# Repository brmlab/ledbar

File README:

eagle: PCB design
arduino: Semi-generic TLC59116 library and ledbar Arduino firmware
host: C frontend
host_python: Python frontend

Both the C frontend and the Python frontend have their pros and cons.
We still use both and it's unclear which one will prevail. Try them
and use the one you like better.

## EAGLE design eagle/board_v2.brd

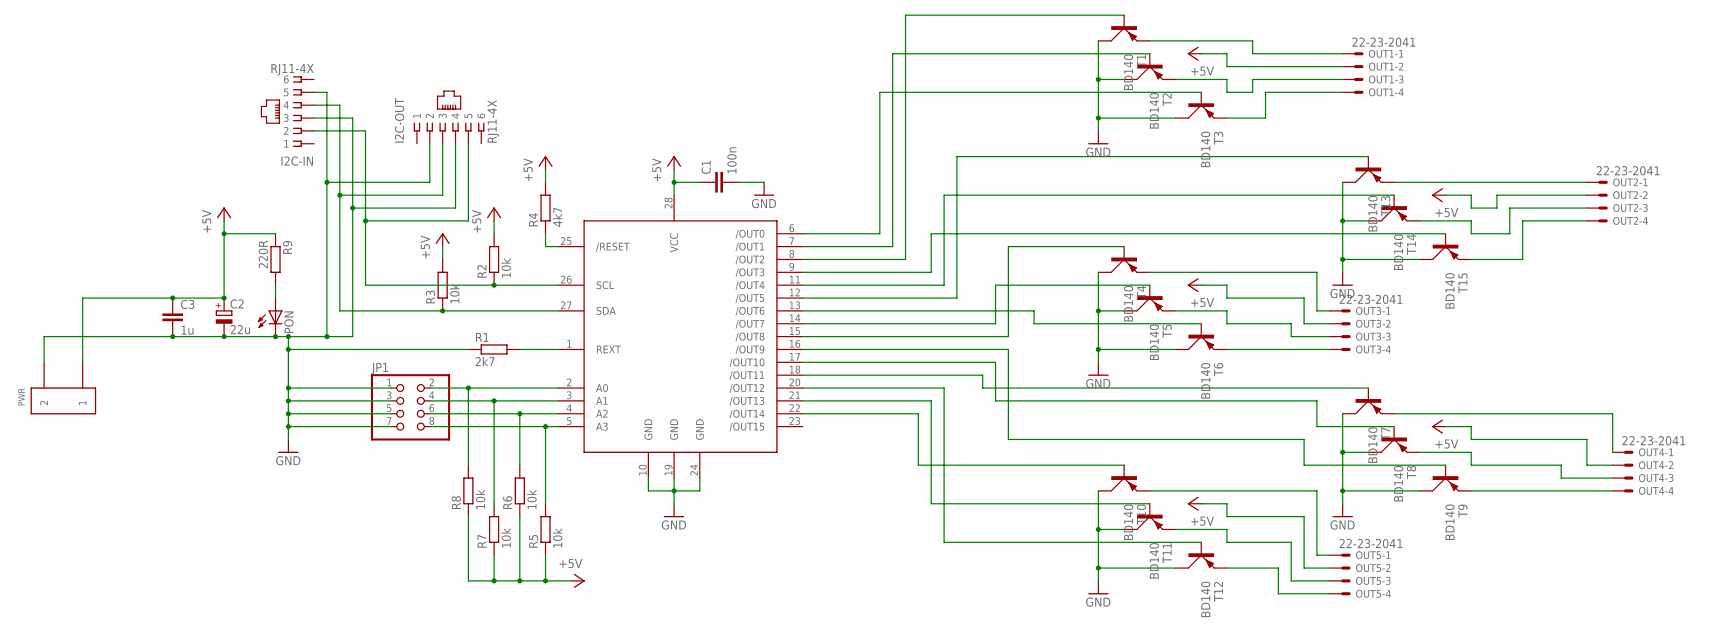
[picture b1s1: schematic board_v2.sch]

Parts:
C1: 100n; C1206
C2: 22u; E2,5-5
C3: 1u; C1206
I2C-IN: RJ11-4X; RJ11-NO_SHIELD
I2C-OUT: RJ11-4X; RJ11-NO_SHIELD; MPN 6609214-3
IC1: TLC59116; TSSOP28
JP1: PINHD-2X4; 2X04
OUT1, OUT2, OUT3, OUT4, OUT5: 22-23-2041
PON: LEDCHIPLED_1206; CHIPLED_1206
PWR: ARK210/2EX
R1: 2k7; R1206
R2, R3, R5, R6, R7, R8: 10k; R1206
R4: 4k7; R1206
R9: 220R; R1206
T1, T2, T3, T4, T5, T6, T7, T8, T9, T10, T11, T12, T13, T14, T15: BD140; TO126AV

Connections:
+5V: C1.1, C2.+, C3.1, IC1.28 (VCC), OUT1.2, OUT2.2, OUT3.2, OUT4.2, OUT5.2, PWR.P$1 (1), R2.2, R3.2, R4.2, R5.1, R6.1, R7.1, R8.1, R9.1
GND: C1.2, C2.-, C3.2, I2C-IN.3, I2C-IN.5, I2C-OUT.2, I2C-OUT.4, IC1.10 (GND), IC1.19 (GND), IC1.24 (GND), JP1.1, JP1.3, JP1.5, JP1.7, PON.C, PWR.P$2 (2), R1.1, T1.C, T2.C, T3.C, T4.C, T5.C, T6.C, T7.C, T8.C, T9.C, T10.C, T11.C, T12.C, T13.C, T14.C, T15.C
unnamed: OUT1.1, T1.E
unnamed: OUT1.3, T2.E
unnamed: OUT1.4, T3.E
unnamed: OUT3.1, T4.E
unnamed: OUT3.3, T5.E
unnamed: OUT3.4, T6.E
unnamed: OUT4.1, T7.E
unnamed: OUT4.3, T8.E
unnamed: OUT4.4, T9.E
unnamed: OUT5.1, T10.E
unnamed: OUT5.3, T11.E
unnamed: OUT5.4, T12.E
unnamed: OUT2.1, T13.E
unnamed: OUT2.3, T14.E
unnamed: OUT2.4, T15.E
unnamed: IC1.9 (/OUT3), T15.B
unnamed: IC1.2 (A0), JP1.2, R8.2
unnamed: IC1.3 (A1), JP1.4, R7.2
unnamed: IC1.4 (A2), JP1.6, R6.2
unnamed: IC1.5 (A3), JP1.8, R5.2
unnamed: IC1.1 (REXT), R1.2
unnamed: IC1.6 (/OUT0), T3.B
unnamed: IC1.7 (/OUT1), T2.B
unnamed: IC1.8 (/OUT2), T1.B
unnamed: IC1.11 (/OUT4), T14.B
unnamed: IC1.12 (/OUT5), T13.B
unnamed: IC1.13 (/OUT6), T6.B
unnamed: IC1.14 (/OUT7), T5.B
unnamed: IC1.15 (/OUT8), T4.B
unnamed: IC1.16 (/OUT9), T9.B
unnamed: IC1.17 (/OUT10), T8.B
unnamed: IC1.18 (/OUT11), T7.B
unnamed: IC1.20 (/OUT12), T12.B
unnamed: IC1.21 (/OUT13), T11.B
unnamed: IC1.22 (/OUT14), T10.B
unnamed: IC1.25 (/RESET), R4.1
unnamed: I2C-IN.2, I2C-OUT.5, IC1.26 (SCL), R2.1
unnamed: I2C-IN.4, I2C-OUT.3, IC1.27 (SDA), R3.1
unnamed: PON.A, R9.2

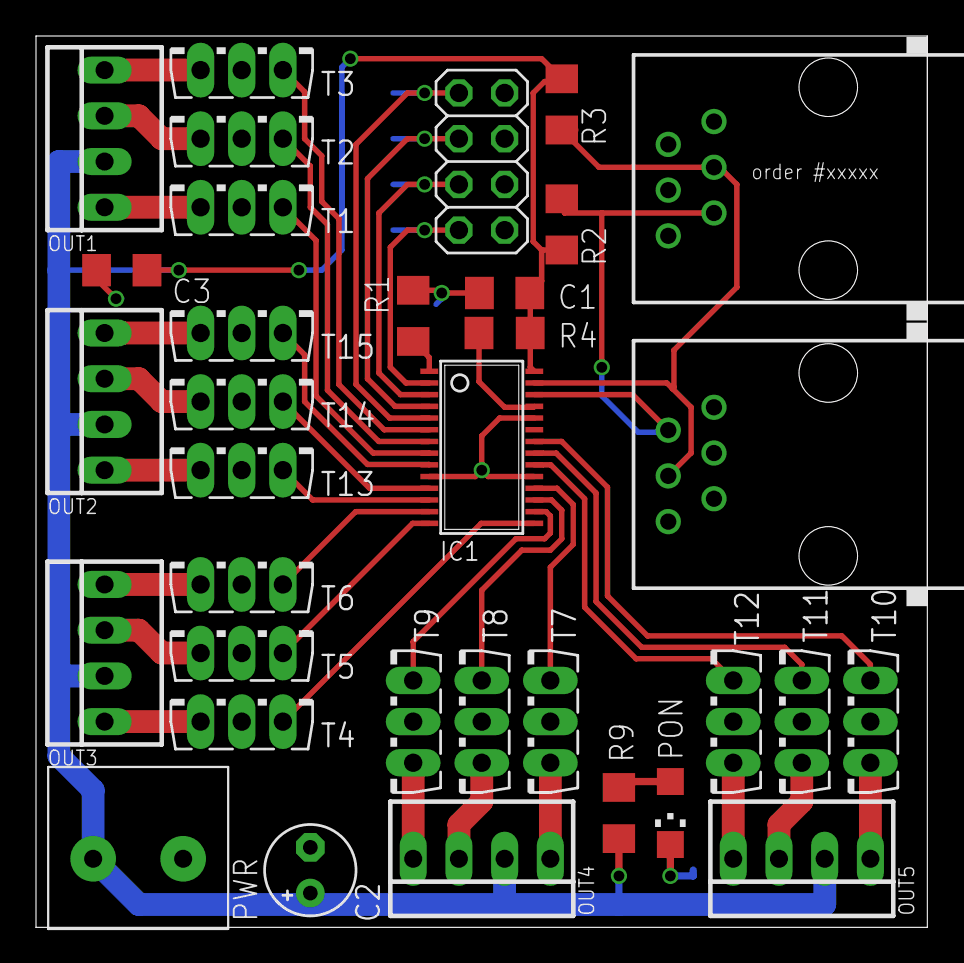
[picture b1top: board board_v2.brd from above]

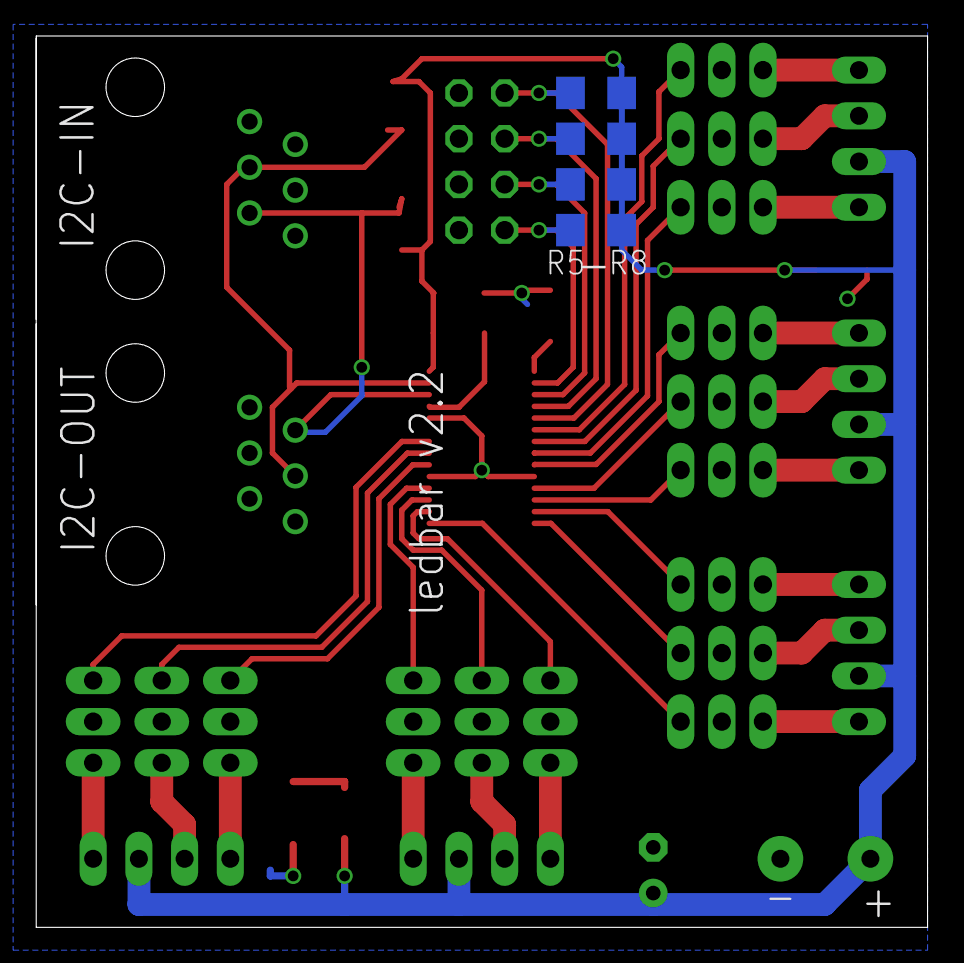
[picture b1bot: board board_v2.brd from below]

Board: 2 copper layers, 49.5 x 49.5 mm, 38 parts (4 on the bottom side), 41 nets.

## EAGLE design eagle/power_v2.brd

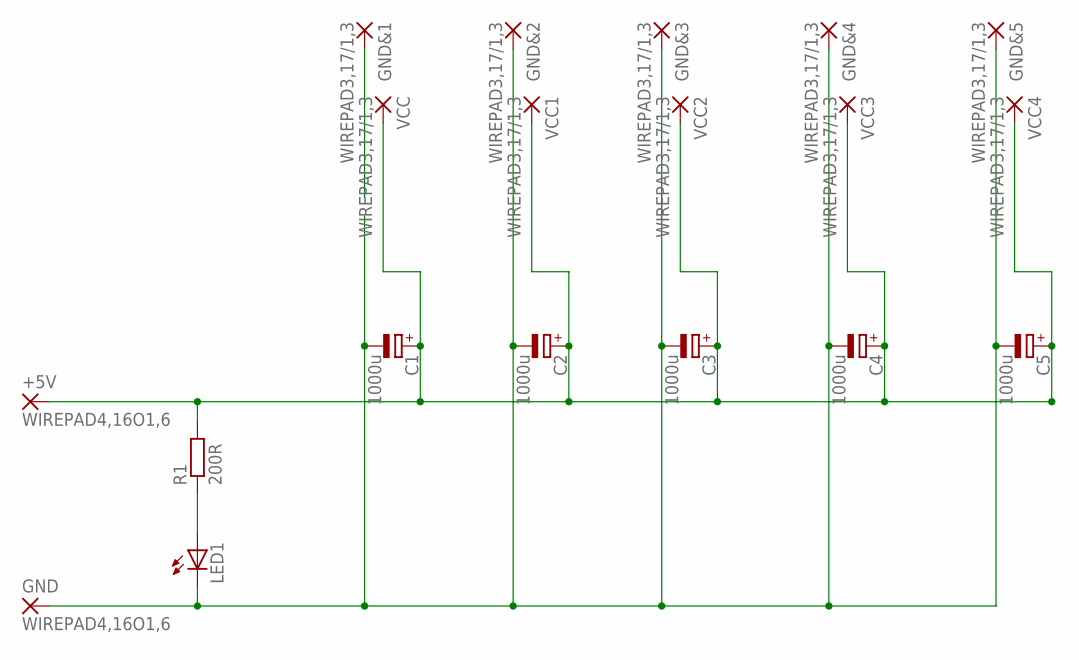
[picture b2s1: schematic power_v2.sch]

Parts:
+5V: WIREPAD4,16O1,6; 4,16O1,6
C1, C2, C3, C4, C5: 1000u; E5-10,5
GND: WIREPAD4,16O1,6; 4,16O1,6
GND&1, GND&2, GND&3, GND&4, GND&5: WIREPAD3,17/1,3; 3,17/1,3
LED1: LED5MM
R1: 200R; R1206
VCC, VCC1, VCC2, VCC3, VCC4: WIREPAD3,17/1,3; 3,17/1,3

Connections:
GND: C1.-, C2.-, C3.-, C4.-, C5.-, GND.1, GND&2.1, GND&3.1, GND&4.1, GND&5.1, LED1.K (C)
unnamed: LED1.A, R1.1
unnamed: +5V.1, C1.+, C2.+, C3.+, C4.+, C5.+, R1.2, VCC.1, VCC1.1, VCC2.1, VCC3.1, VCC4.1

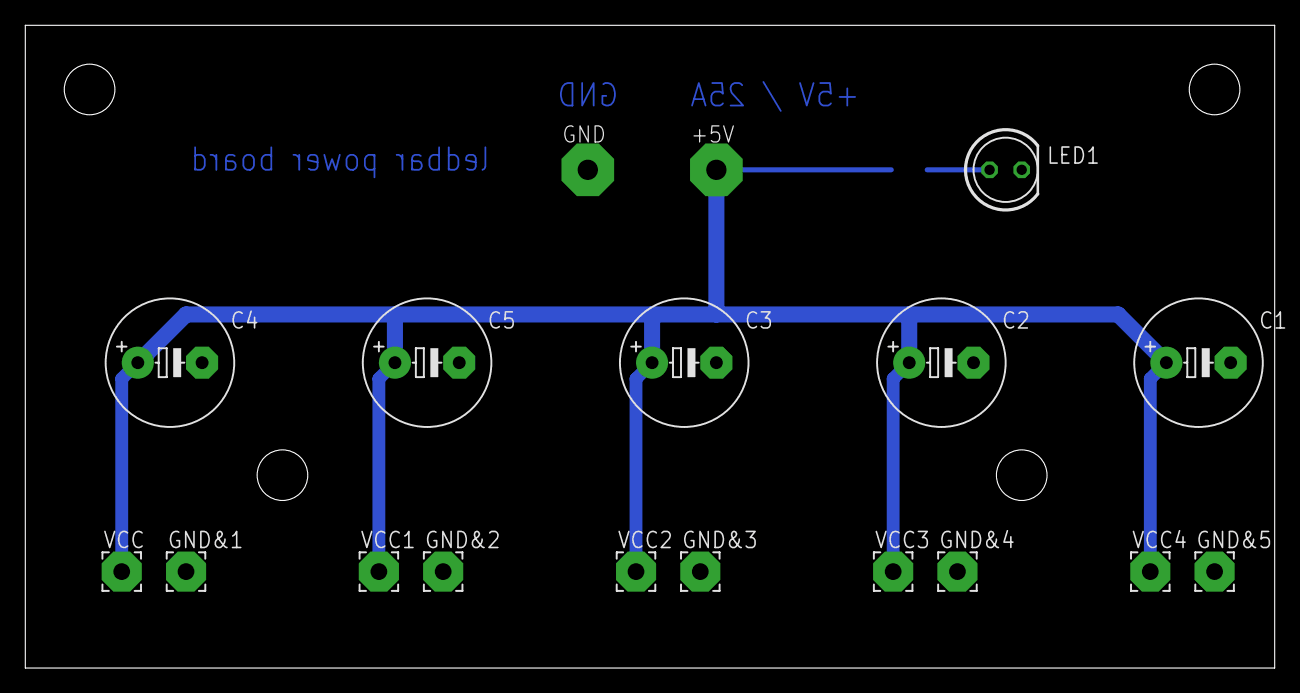
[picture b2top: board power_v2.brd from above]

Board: 2 copper layers, 98.7 x 50.8 mm, 19 parts (1 on the bottom side), 3 nets.

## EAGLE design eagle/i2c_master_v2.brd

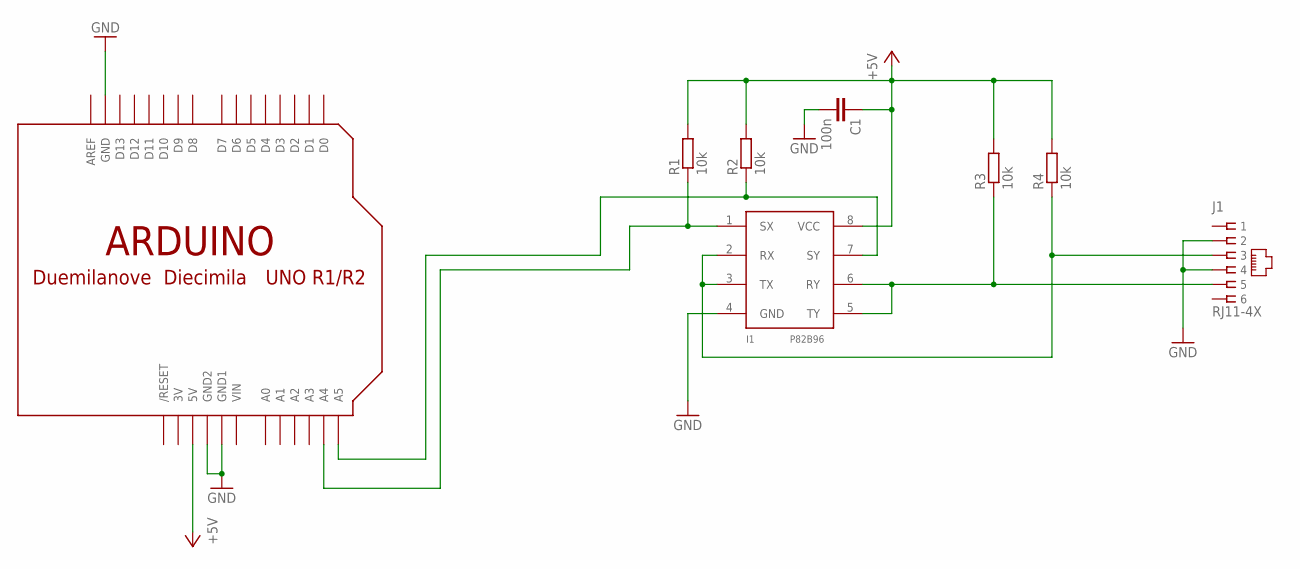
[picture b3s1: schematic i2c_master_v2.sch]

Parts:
C1: 100n; C1206
I1: P82B96; SOIC8
J1: RJ11-4X; RJ11-NO_SHIELD
R1, R2, R3, R4: 10k; M1206
U$1: ARDUINO-NOHOLE

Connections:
3V: U$1.3V
+5V: C1.1, I1.8 (VCC), R1.2, R2.2, R3.2, R4.2, U$1.5V
GND: C1.2, I1.4 (GND), J1.2, J1.4, U$1.GND, U$1.GND1, U$1.GND2
unnamed: I1.7 (SY), R2.1, U$1.A5
unnamed: I1.1 (SX), R1.1, U$1.A4
unnamed: I1.5 (TY), I1.6 (RY), J1.5, R3.1
unnamed: I1.2 (RX), I1.3 (TX), J1.3, R4.1
VIN: U$1.VIN

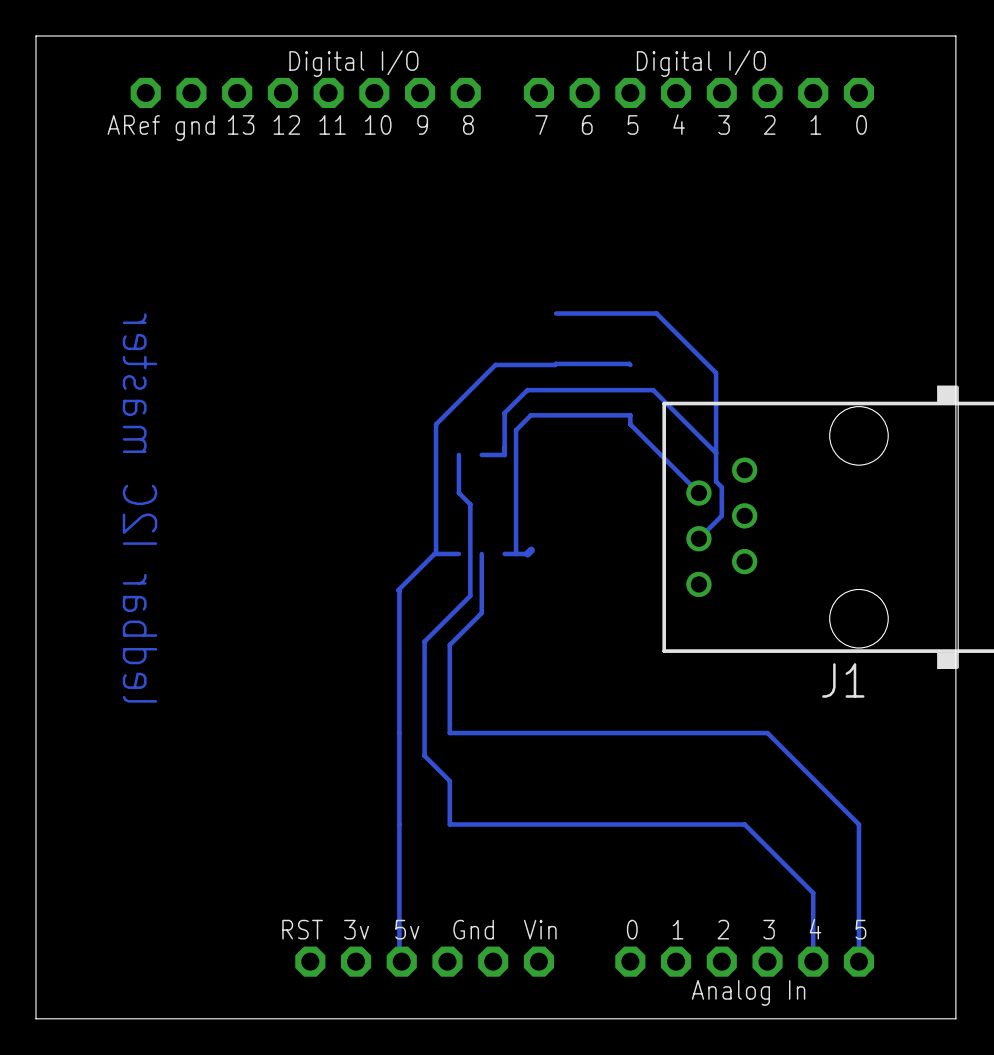
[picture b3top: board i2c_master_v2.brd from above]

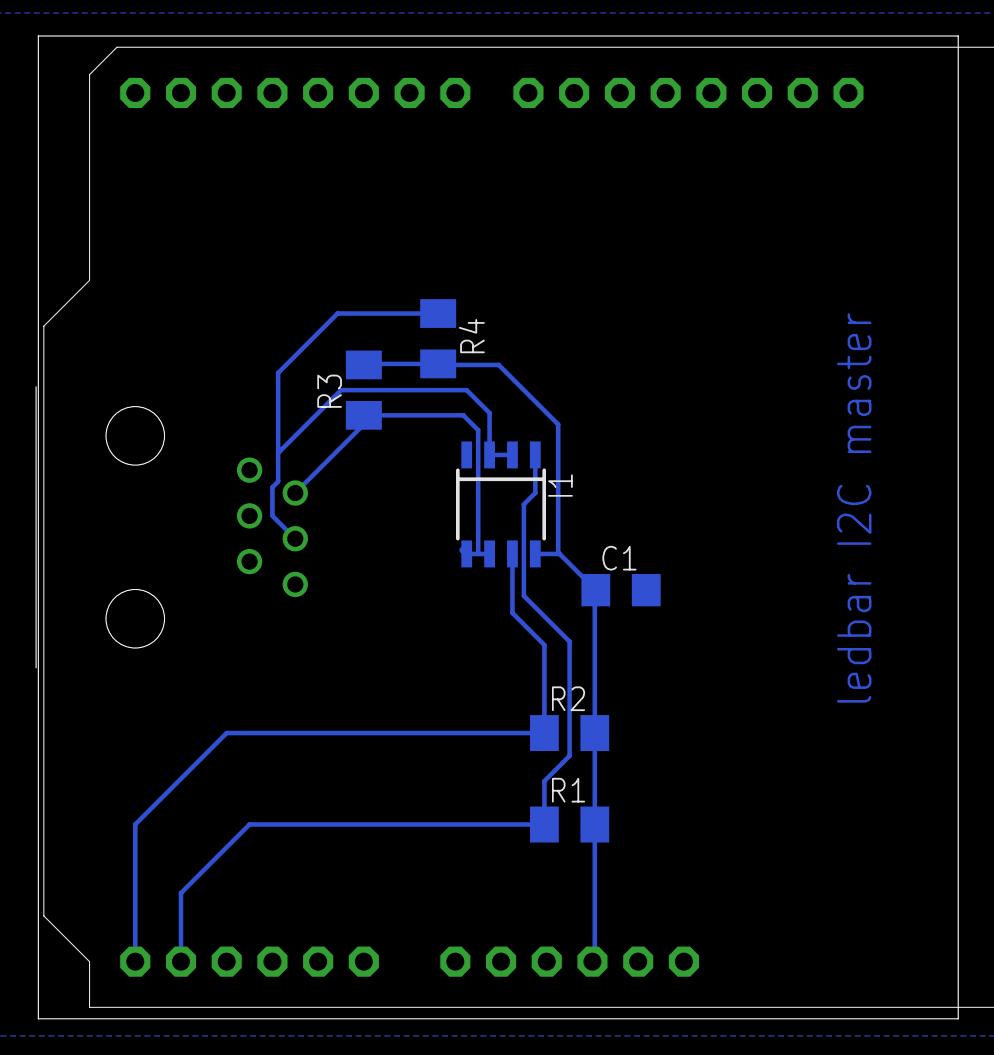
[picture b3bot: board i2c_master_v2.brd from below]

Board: 2 copper layers, 51.1 x 54.6 mm, 8 parts (6 on the bottom side), 6 nets.

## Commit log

2010-12-03 fix typo
2010-12-03 add simple rainbow as well
2010-12-04 add morse code program
2010-12-05 miniPOV
2010-12-06 add 2 type of clocks
2011-04-22 Move host software to host/ subdirectory.
2011-04-22 arduino/autonomous.pde: Add the autonomous LED control sketch
2011-09-20 Various changes to host/ledbar.c
2011-09-20 Current version of the autonomous sketch
2011-09-20 Added option to write the output to file
2011-09-20 Changed the number of pixels to 10
2011-09-20 Factor out #define FPS, sleep -> wait
2011-09-20 Flush fp after one complete frame
2011-09-20 Sleep at the beginning to give time for Arduino to settle
2011-09-20 POV: Speed up
2011-09-20 Set fp baudrate to 38400
2011-09-20 Sketch for computer-controlled ledbar
2011-09-21 The sleep is only needed if we output data
2011-09-21 Added script which sends its stdin to serial
    * It groups its input into batches of 3*(# of boxes) bytes
2011-09-21 Added script which shows simulation of ledbar
    * depends on pygame, which is something like wrapper around SDL
    * it gets its input from stdin, displays it and sends it to stdout, so some other script can work with it further
2011-09-21 Added class simplifiing ledbar output
    * also added rainbow.py, which uses this class to create rainbow effect
2011-09-23 Added Python equalizer effect generator
    * It uses input from microphone and displays colors based on the frequencies present in the input
2011-09-26 Fixed synchronization bugs in Python version
2011-10-02 4 new programs: green vs blue (a) and crossfades (s,d,f)
2011-11-16 eagle files v2.1 - fixed clearance between pads and signal routes
2011-11-16 fix build
2011-11-17 ledbar-shield v2
2011-11-17 more ledbar-shield fixes
2011-11-17 ledbar board v2.2
2011-11-17 ledbar howto poster
2012-05-05 New design of boards using TLC59116
2012-05-05 power board v2
2012-05-05 ignore temporary .lbr files
2012-05-05 i2c master shield for arduino
2012-05-05 i2c master shield for arduino - minor clearance fix
2012-05-07 board chaining connectors
2012-05-08 cinch -> svorkovnice
2012-05-15 moar changes
2012-06-27 Convert arduino autonomous.pde to new TLC59116, single-TLC configuration
2012-06-28 i2c in crossover; removed jumper wires
2012-06-30 autonomous: Support multiple TLCs
2012-06-30 arduino: Move ledbar configuration from autonomous to common ledbar.h
2012-06-30 arduino: Update controlled for new TLCs
2012-06-30 Arduino autonomous grey(): Lengthen breathing effect
2012-06-30 Arduino controlled: Fix ledbar addressing
2012-06-30 Arduino controlled: Wait for burst, then read whole led block
2012-06-30 Controlled: Switch to baudrate 115200
2012-06-30 host_python/equalizer: Ratelimit updates
2012-06-30 arduino/ledbar.h: Limit to two boards for now
2012-07-20 Sketches Makefile: depend on ledbar.h
2012-07-20 Calibrate LED channels
2012-07-20 autonomous: Use new Ledbar::setAllPinPWM() method, much faster LED control
2012-07-20 autonomous: Make rainbow() and grey() much slower and smoother
2012-07-20 autonomous: Bracket channels by cmin[] in addition to cmax[]; red channel requires some minimal trigger level
2012-07-20 autonomous: factor out setAllPinPWM() loop to ledbar.h:setbyc()
2012-07-20 Arduino controlled: Use setbyc(), cmin[]
2012-07-20 Communication speed is 115200
2012-07-20 Arduino controlled: Get rid of debug prints, fix Serial.available() wait
2012-07-24 board v2.1
    * PCB size has been optimized
    * Layout has been redesigned to minimize current loop area.
2012-07-24 board - increased via size
2012-07-24 board - png image updated
2012-08-19 host_python: Change default number of LEDs to 20
2012-08-19 host: Also change default number of LEDs to 20
2012-08-19 arduino: Change firmware to use 20 LEDs instead of 10; we have 4 working TLC PCBs\!
2012-08-19 Change serial speed from 115200 to 57600
    With non-blinkenlight setups, 115200 communication is not reliable at all. About 26kbaud should be enough bandwidth anyway.
2012-08-19 README: Add brief description of ledbar components
2012-08-19 arduino: Change cmin[] semantics - pwm level of channel level 1, not 0
    Should eliminate dim red light for black pixels.
2012-08-19 equalizer.py: Parse commandline parameters (-n PIXELS, -h)
2012-08-19 equalizer.py: Commandline parameter -s for mode with slower updates
2012-08-19 equalizer.py: In non-slow mode, spread values more in the [0,1] interval to account for low dynamic range of ledbar pixels
2012-08-19 equalizer.py: Raise MIN_FREQ from 20 to 50; that's where range of most microphones starts
2012-08-19 equalizer.py: Commented-out example of monochromatic mode
2012-08-19 equalizer.py: Rename slow (-s) to lazy (-l)
2012-08-19 equalizer.py -s: Symmetric mode (centered)
2012-08-21 board v2.2
2012-08-21 board v2.2 - silkscreen cleanup
2012-08-21 board v2.2 - gerber files for fusion pcb service, top & bottom pcb preview images
2012-08-31 Board v2.2 - power-on LED added; minor adjustments to silkscreen (version, brmlab logo)
2012-09-14 equalizer: MIN_FREQ 50 -> 30
2012-09-14 equalizer get_color: Better thresholding devised by Nephirus
2012-09-14 equalizer: Fix loss of intensity in higher frequencies due to wider ranges
2012-09-14 equalizer: Reduce lag caused by averaging by giving less weight to older samples
2012-09-14 equalizer: Shorten CHUNK_SIZE, partially compensate with HISTORY_SIZE
    CHUNK_SIZE will make the FFT buckets bigger, causing better space usage
    by pixels; it will also reduce latency. with original HISTORY_SIZE,
    there is too much flicker.
2012-10-17 cellular.py: a simple 2D cellular automata implementation
2012-10-17 cellular.py: Colors, starting conditions, any rule number
2012-10-30 cellular.py: Implement totalistic celluar automata.
2012-10-30 cellular.py: impleement a individual color mode. Default setting is pretty vivid and good to go.
2012-11-16 Add synchronization byte \xAC at the beginning of RGB burst
2012-11-21 silkscreen update
2012-11-21 gerber files
2012-11-29 Basic multiplexing (use equalizer.py when music is playing, rainbow.py otherwise)
2012-11-30 Code reformatting and simple TUI
2012-11-30 Don't display stderr, path fix
2012-12-07 Added a program for outputting the CZK exchange rates onto a 5x4 matrix
2012-12-10 Implemented a 2d soothing rainbow
2012-12-22 nicer equalizer!!
2012-12-22 equalizer: minor exception handling
2012-12-22 host_python/equalizer.py: Switch HUE default, add -H commandline option
2012-12-22 host_python/rainbow2d.py: Essential fixups; needs more work
2012-12-22 host_python/cellular.py: +x
2012-12-22 Update host_python/equalizer.py
    fix range of autocorrelation
2012-12-23 rainbow2d: nicer distance function !!
2013-01-14 board v2.1 partlist
2013-01-14 board v2.2 partlist
2013-12-30 rainbow2d: Simplify
2013-12-30 equalizer: MIN_FREQ 30 -> 50
2013-12-30 equalizer: Some old change I don't understand now
2013-12-30 equalizer: Fix high CPU usage by waiting a tiny bit in case of no data fetched from soundcard
2014-06-23 Eagle files moved to eagle project
